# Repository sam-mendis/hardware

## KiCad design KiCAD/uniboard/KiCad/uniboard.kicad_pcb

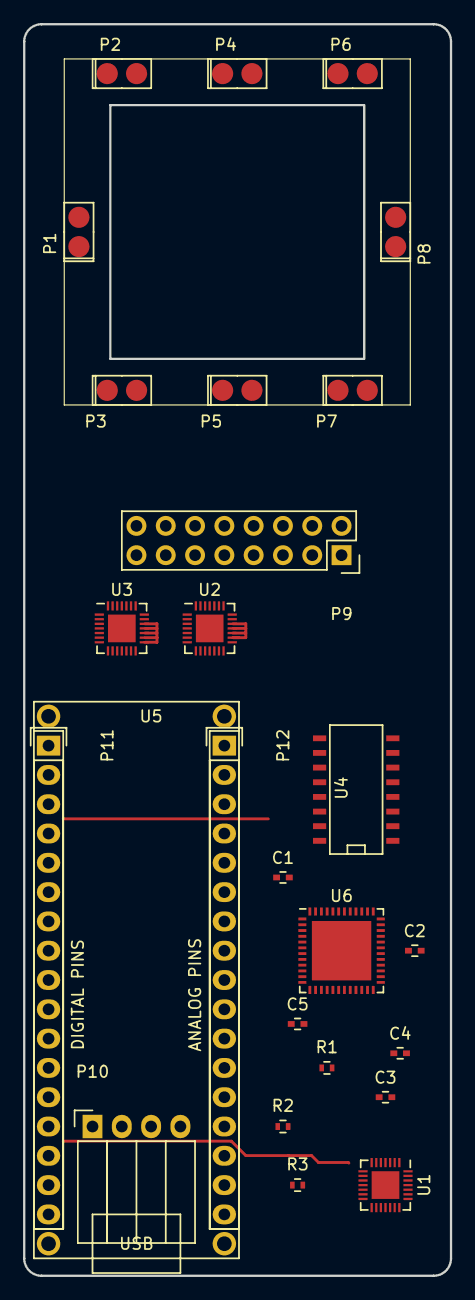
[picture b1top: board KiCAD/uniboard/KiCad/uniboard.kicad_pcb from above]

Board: 2 copper layers, 37.0 x 108.5 mm, 26 parts (0 on the bottom side), 37 nets.

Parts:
C1, C2, C5: 0.1uF; C_0402
C3: 47uF; C_0402
C4: 2.2uF; C_0402
P1, P2, P3, P4, P5, P6, P7, P8: 2x1_pogo_pin
P9: CONN_02X08; Socket_Strip_Straight_2x08
P10: CONN_01X04; Socket_Strip_Angled_1x04
P11, P12: CONN_01X17; Socket_Strip_Straight_1x17
R1: 0R1; R_0402
R2, R3: 100k; R_0402
U1, U2, U3: MAX14662; QFN-28-1EP_4x4mm_Pitch0.4mm
U4: PCF8574; SO-16-N
U5: ARDUINO_MICRO; arduino_micro
U6: LTC2345-18; QFN-48-1EP_7x7mm_Pitch0.5mm

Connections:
+3V3: C5.1, P12.16, R2.1, R3.1, U1.1, U1.22, U1.26, U2.1, U2.22, U2.26, U3.1, U3.22, U3.26, U4.1, U4.3, U4.16, U6.31
+5V: C1.1, P12.6, U6.42, U6.43
/Reset: P11.5, P12.5
ADC_CNV: U4.7, U6.24
A_AL_I: P1.1, P9.1, U2.2
A_AL_V: P1.2, P9.2, U3.2
A_AR_I: P8.1, P9.15, U2.9
A_AR_V: P8.2, P9.16, U3.9
A_B0_I: P2.1, P9.3, U2.3
A_B0_V: P2.2, P9.4, U3.3
A_B1_I: P3.1, P9.5, U2.4
A_B1_V: P3.2, P9.6, U3.4
A_B2_I: P4.1, P9.7, U2.5
A_B2_V: P4.2, P9.8, U3.5
A_B3_I: P5.1, P9.9, U2.6
A_B3_V: P5.2, P9.10, U3.6
A_B4_I: P6.1, P9.11, U2.7
A_B4_V: P6.2, P9.12, U3.7
A_B5_I: P7.1, P9.13, U2.8
A_B5_V: P7.2, P9.14, U3.8
CS_B: U1.23, U4.5
GND: C1.2, C2.2, C3.2, C4.1, C5.2, P11.6, P12.4, R1.2, U1.11, U1.25, U2.11, U2.25, U3.11, U3.25, U4.2, U4.8, U6.15, U6.16, U6.17, U6.18, U6.20, U6.22, U6.23, U6.30, U6.41, U6.44, U6.45, U6.46, U6.49
I+: P10.1, U1.2, U2.15, U2.16, U2.17, U2.18, U2.19, U2.20
I-: P10.4, U1.5, U2.14, U2.21
MISO: P12.2, U6.25
MOSI: P11.1, U1.27, U2.27, U3.27, U6.37
unnamed: C2.1, U6.19
unnamed: C3.1, U6.21
unnamed: C4.2, U6.40
unnamed: U2.23, U3.28
SCK: P12.1, U1.24, U2.24, U3.24, U6.29
SCL: P11.8, R3.2, U4.14
SDA: P11.7, R2.2, U4.15
SM_CS: U3.23, U4.4
V+: P10.2, U1.3, U3.15, U3.16, U3.17, U3.18, U3.19, U3.20
V-: P10.3, U1.4, U3.14, U3.21
VADC_CS: U4.6, U6.39

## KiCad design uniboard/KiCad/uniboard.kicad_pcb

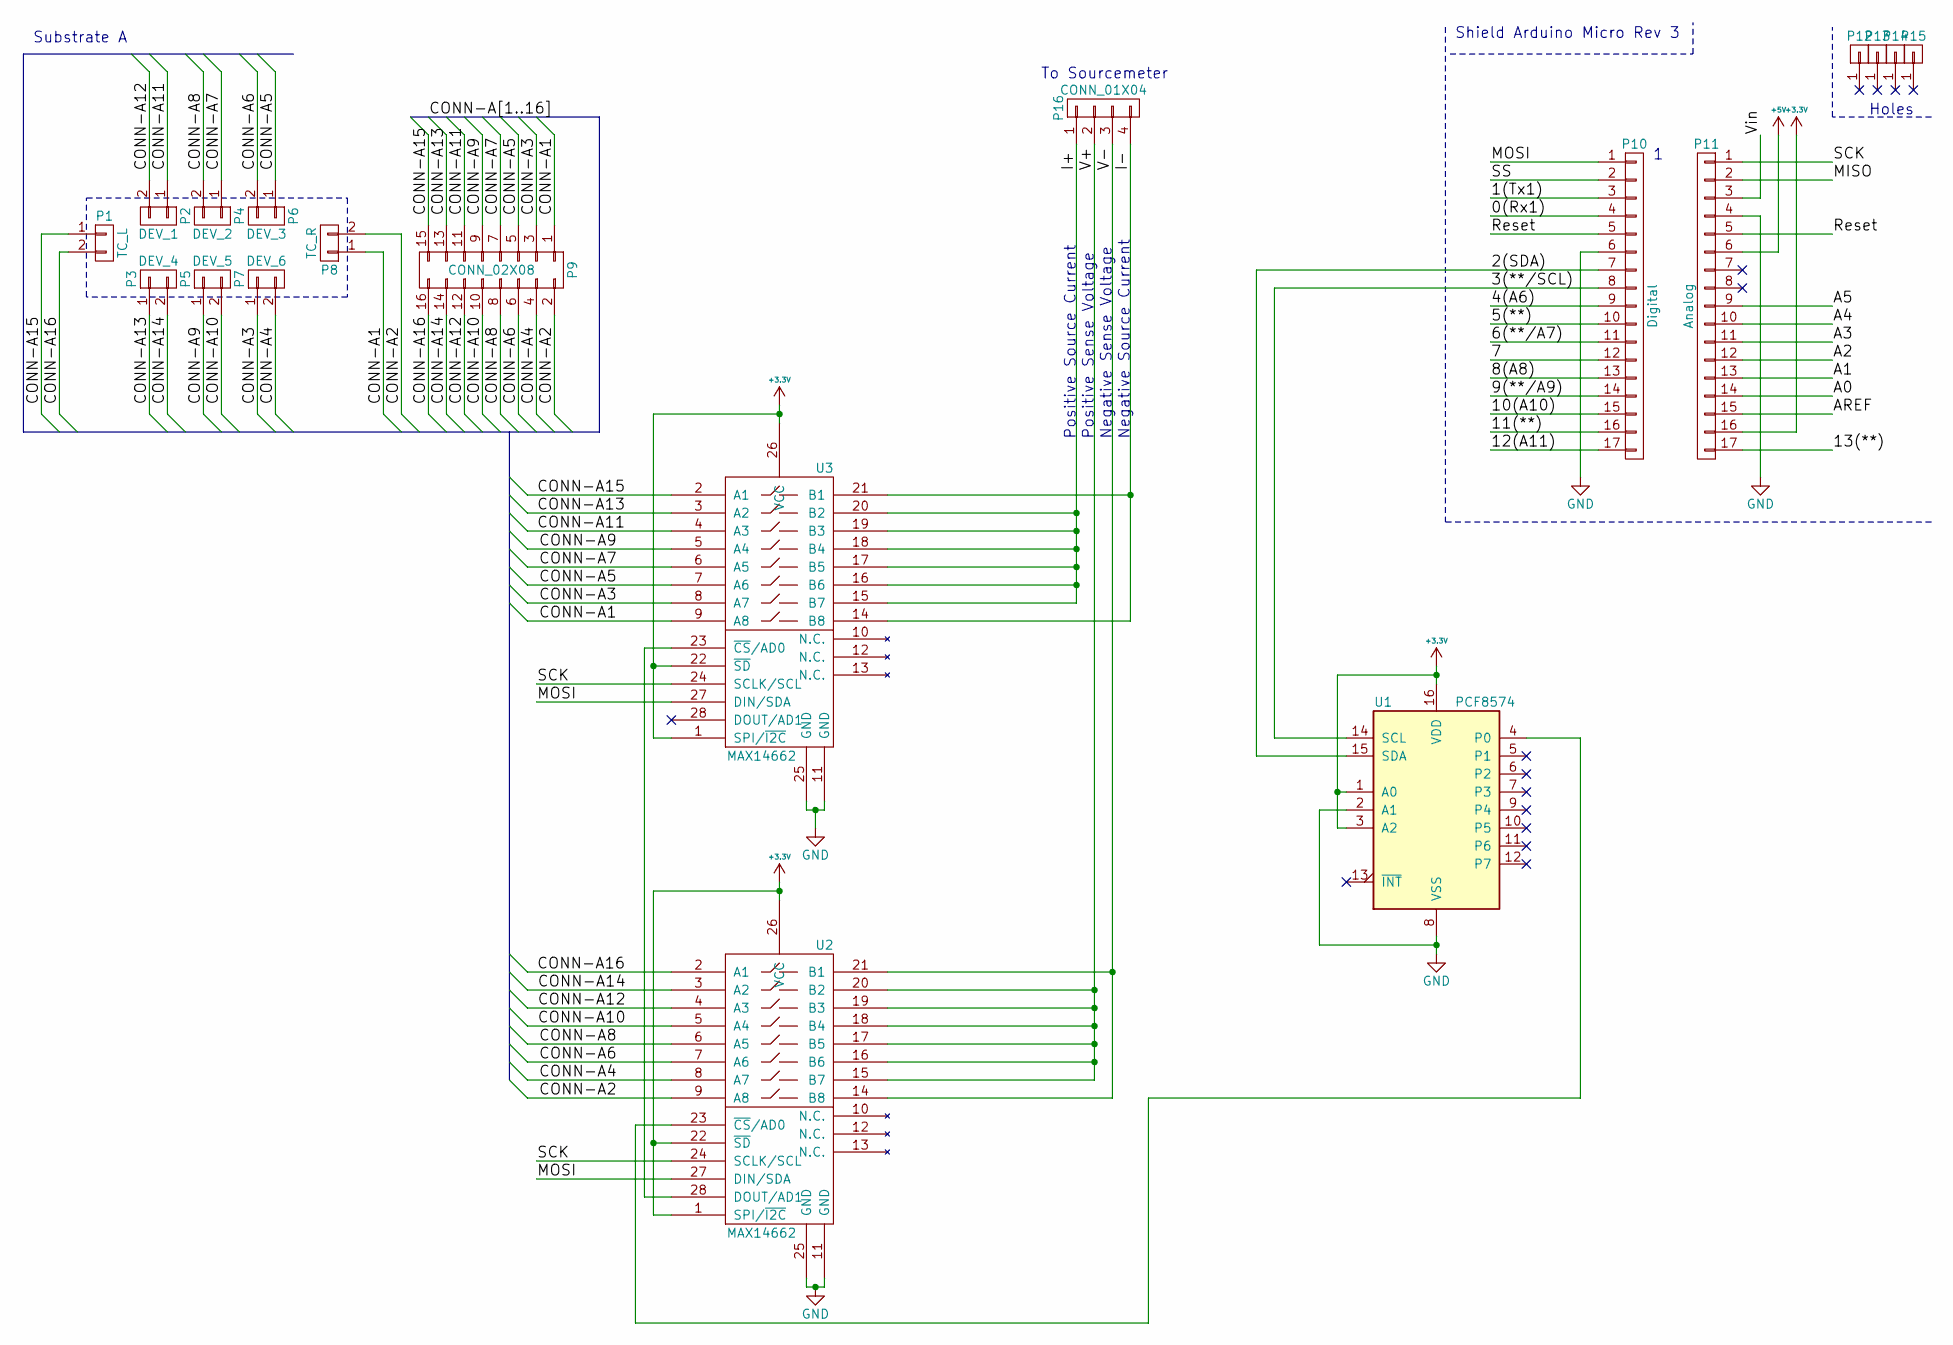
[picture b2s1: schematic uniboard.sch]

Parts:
P1, P2, P3, P4, P5, P6, P7, P8: 2x1_pogo_pin
P9: CONN_02X08; Socket_Strip_Straight_2x08
P10: Digital; Socket_Strip_Arduino_1x17
P11: Analog; Socket_Strip_Arduino_1x17
P12, P13, P14, P15: CONN_01X01; 1pin_Micro
P16: CONN_01X04; PhoenixContact_MSTB-GF_04x5.00mm_Angled_ThreadedFlange_Moun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
U1: PCF8574; SO-16-N
U2, U3: MAX14662; UQFN-28-1EP_4x4mm_Pitch0.4mm

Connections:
+3V3: P11.16, U1.1 (A0), U1.3 (A2), U1.16 (VDD), U2.1 (SPI/~I2C), U2.22 (~SD), U2.26 (VCC), U3.1 (SPI/~I2C), U3.22 (~SD), U3.26 (VCC)
+5V: P11.6
/0(Rx1): P10.4
/1(Tx1): P10.3
/2(SDA): P10.7, U1.15 (SDA)
/3(**/SCL): P10.8, U1.14 (SCL)
/4(A6): P10.9
/5(**): P10.10
/6(**/A7): P10.11
/7: P10.12
/8(A8): P10.13
/9(**/A9): P10.14
/10(A10): P10.15
/11(**): P10.16
/12(A11): P10.17
/13(**): P11.17
/A0: P11.14
/A1: P11.13
/A2: P11.12
/A3: P11.11
/A4: P11.10
/A5: P11.9
/AREF: P11.15
/CONN-A1: P8.1, P9.1, U3.9 (A8)
/CONN-A2: P8.2, P9.2, U2.9 (A8)
/CONN-A3: P7.1, P9.3, U3.8 (A7)
/CONN-A4: P7.2, P9.4, U2.8 (A7)
/CONN-A5: P6.1, P9.5, U3.7 (A6)
/CONN-A6: P6.2, P9.6, U2.7 (A6)
/CONN-A7: P4.1, P9.7, U3.6 (A5)
/CONN-A8: P4.2, P9.8, U2.6 (A5)
/CONN-A9: P5.1, P9.9, U3.5 (A4)
/CONN-A10: P5.2, P9.10, U2.5 (A4)
/CONN-A11: P2.1, P9.11, U3.4 (A3)
/CONN-A12: P2.2, P9.12, U2.4 (A3)
/CONN-A13: P3.1, P9.13, U3.3 (A2)
/CONN-A14: P3.2, P9.14, U2.3 (A2)
/CONN-A15: P1.1, P9.15, U3.2 (A1)
/CONN-A16: P1.2, P9.16, U2.2 (A1)
/I+: P16.1, U3.15 (B7), U3.16 (B6), U3.17 (B5), U3.18 (B4), U3.19 (B3), U3.20 (B2)
/I-: P16.4, U3.14 (B8), U3.21 (B1)
/MISO: P11.2
/MOSI: P10.1, U2.27 (DIN/SDA), U3.27 (DIN/SDA)
/Reset: P10.5, P11.5
/SCK: P11.1, U2.24 (SCLK/SCL), U3.24 (SCLK/SCL)
/SS: P10.2
/V+: P16.2, U2.15 (B7), U2.16 (B6), U2.17 (B5), U2.18 (B4), U2.19 (B3), U2.20 (B2)
/V-: P16.3, U2.14 (B8), U2.21 (B1)
/Vin: P11.3
GND: P10.6, P11.4, U1.2 (A1), U1.8 (VSS), U2.11 (GND), U2.25 (GND), U3.11 (GND), U3.25 (GND)
unnamed: U1.4 (P0), U2.23 (~CS~/AD0)
unnamed: U2.28 (DOUT/AD1), U3.23 (~CS~/AD0)

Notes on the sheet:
Substrate A
Shield Arduino Micro Rev 3
Holes
To Sourcemeter
Negative Sense Voltage
Positive Sense Voltage
Negative Source Current
Positive Source Current

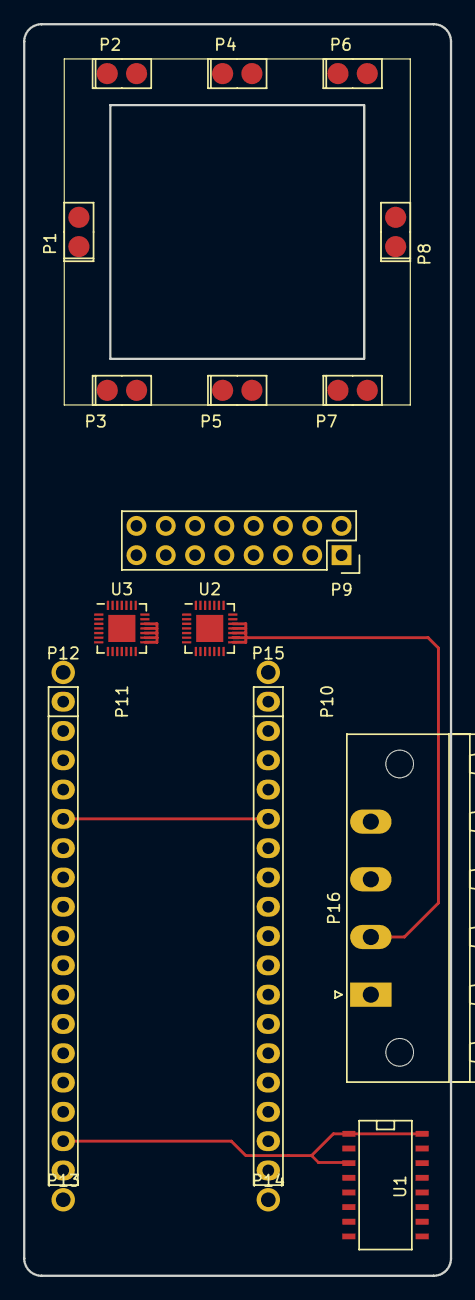
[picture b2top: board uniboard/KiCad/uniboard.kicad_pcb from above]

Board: 2 copper layers, 37.0 x 108.5 mm, 19 parts (0 on the bottom side), 29 nets.
